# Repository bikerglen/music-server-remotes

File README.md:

Mopidy Music Server and Pianobar Player Remote Track/Artist/Album Display

Mopidy Music Server Remote Control

This repository contains the enclsoure designs, circuit board designs, and software for a Mopidy / Pianobar remote track / artist / album display and a Mopidy remote playback control. Both are based on Particle Photons and connect to the Linux server hosting the applications using Wi-Fi. The display uses scrolling 14-segment LED displays for a retro look. The remote control uses custom-labeled NKK pushbutton switches.

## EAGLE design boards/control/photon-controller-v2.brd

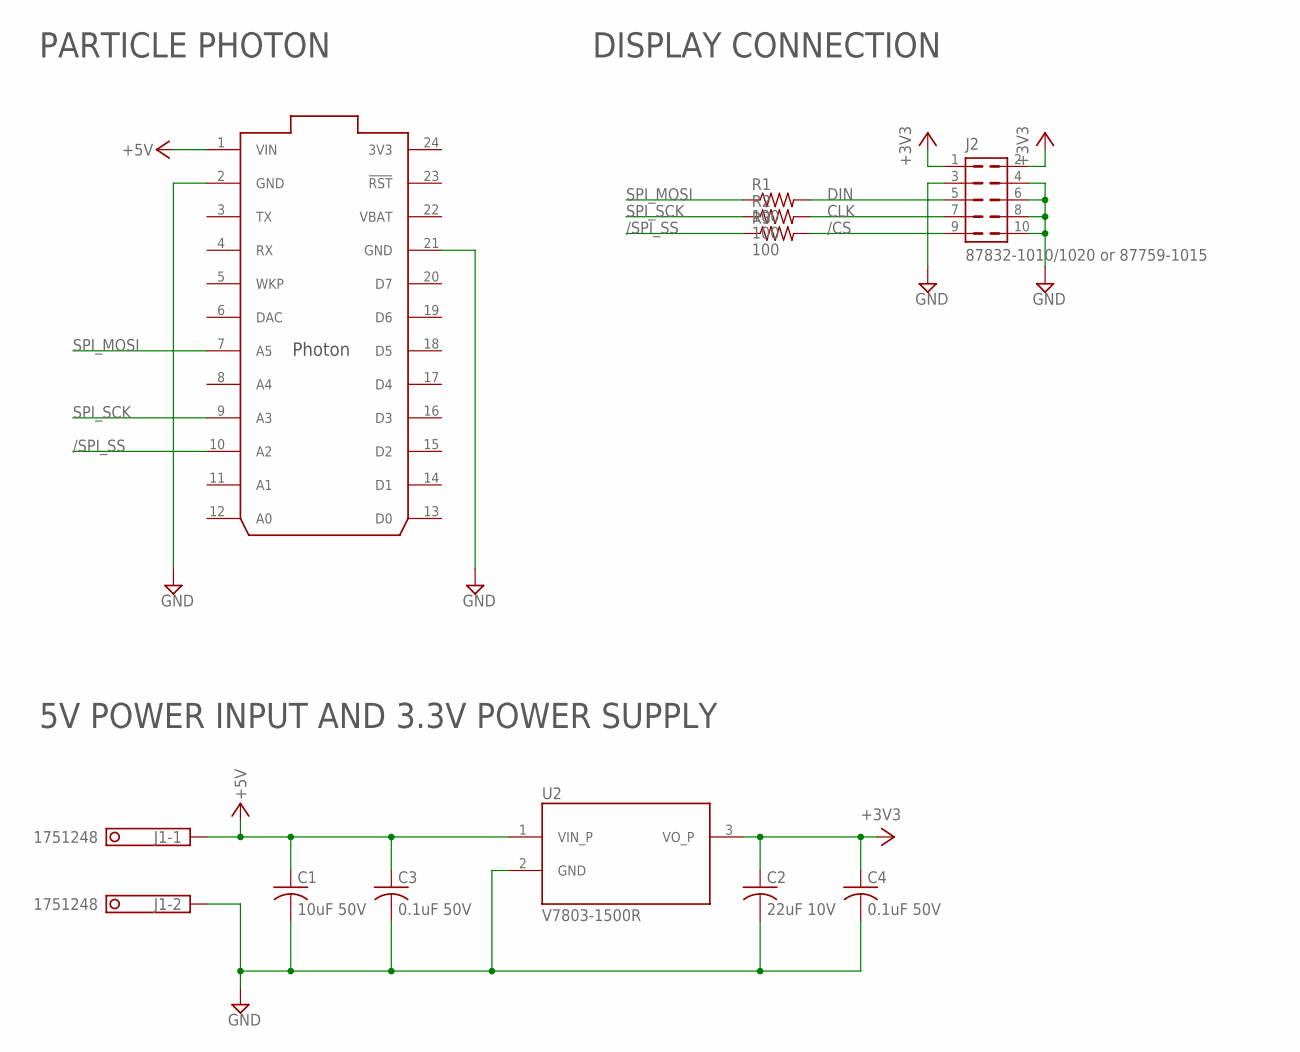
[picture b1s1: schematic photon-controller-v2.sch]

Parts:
C1: 10uF 50V; C1210K; MFR_PART_NO C1210C106K5RACTU
C2: 22uF 10V; C1206K; MFR_PART_NO C1206C226K8RAC7800
C3, C4: 0.1uF 50V; C1206K; MFR_PART_NO C1206S104M5RACTU
J1: 1751248
J2: 87832-1010/1020 or 87759-1015; 87832-10
R1, R2, R3: 100; R1206
U1: PHOTON_WITH_HEADERS; PHOTON
U2: V7803-1500R; CONV_V7803-1500R

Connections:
3V3: U1.24 (3V3)
+3V3: C2.1, C4.1, J2.1, J2.2, U2.3 (VO_P)
+5V: C1.1, C3.1, J1.1, U1.1 (VIN), U2.1 (VIN_P)
/CS: J2.9, R3.2
/SPI_SS: R3.1, U1.10 (A2)
CLK: J2.7, R2.2
DIN: J2.5, R1.2
GND: C1.2, C2.2, C3.2, C4.2, J1.2, J2.3, J2.4, J2.6, J2.8, J2.10, U1.2 (GND), U1.21 (GND), U2.2 (GND)
SPI_MOSI: R1.1, U1.7 (A5)
SPI_SCK: R2.1, U1.9 (A3)
VBAT: U1.22 (VBAT)

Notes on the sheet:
5V POWER INPUT AND 3.3V POWER SUPPLY
PARTICLE PHOTON
DISPLAY CONNECTION

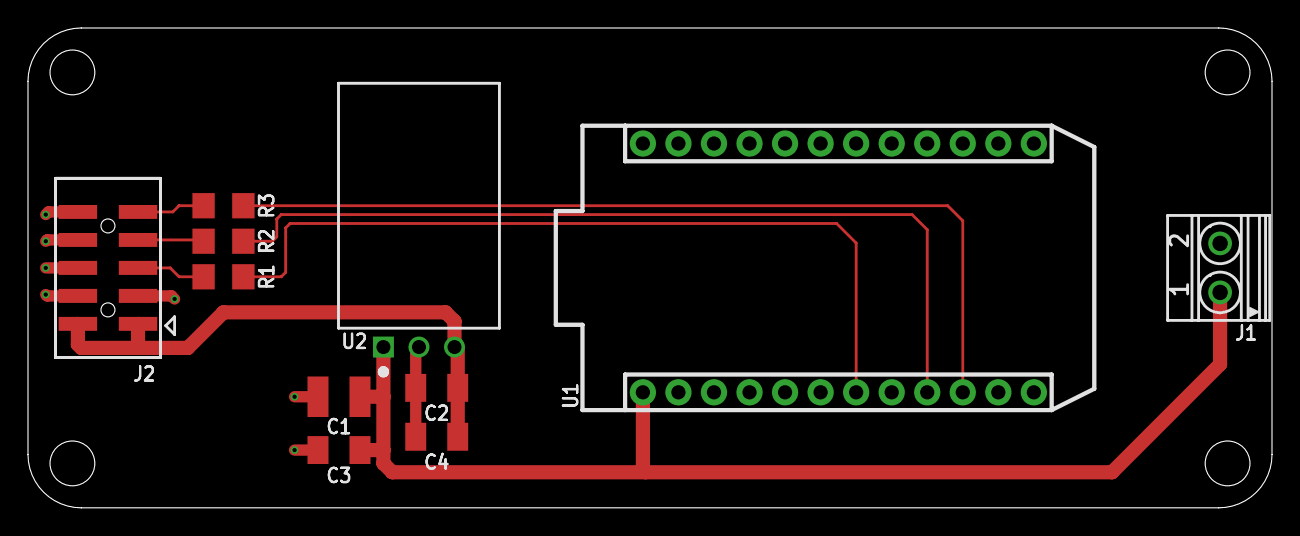
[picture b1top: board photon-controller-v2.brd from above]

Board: 2 copper layers, 88.9 x 34.3 mm, 11 parts (0 on the bottom side), 9 nets.

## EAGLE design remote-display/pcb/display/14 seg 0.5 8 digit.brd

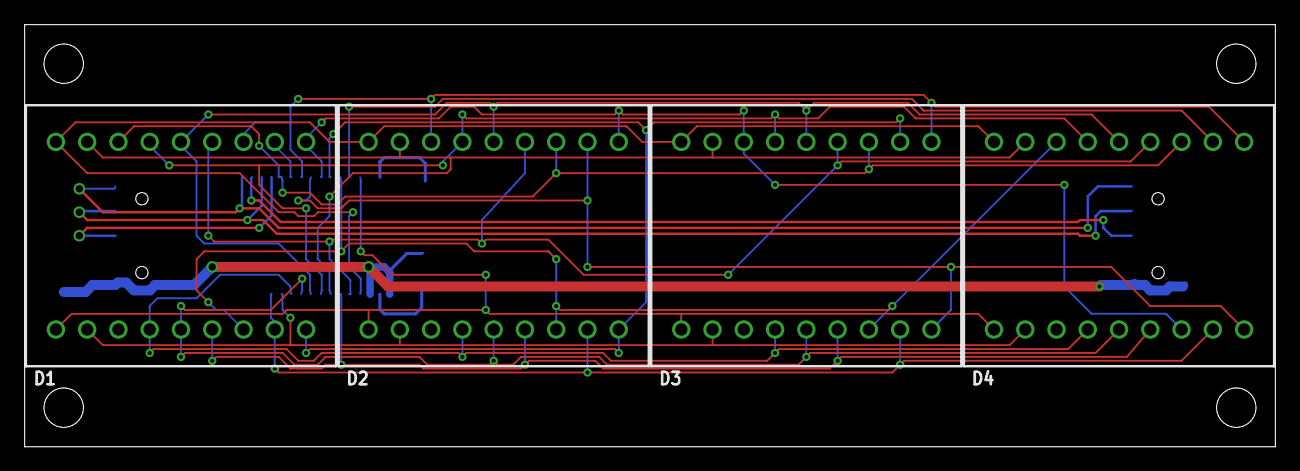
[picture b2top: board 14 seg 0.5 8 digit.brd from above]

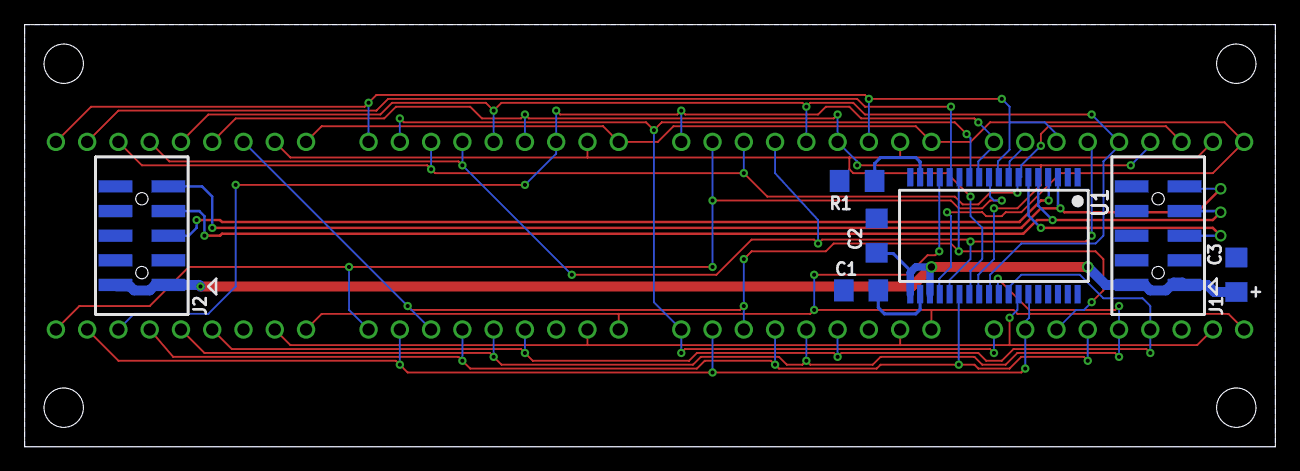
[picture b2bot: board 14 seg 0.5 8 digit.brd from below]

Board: 2 copper layers, 101.6 x 34.3 mm, 11 parts (7 on the bottom side), 27 nets.

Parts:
C1: 22pF; C1206
C2: 0.1uF; C1206
C3: 47uF 10V AVX F931A476MAA; C1206
D1, D2, D3, D4: PCD54-11EWA; PDC54-11
J1, J2: 87832-1010/1020 or 87759-1015; 87832-10
R1: 56k; R1206
U1: MAX6954AAX; MAXIM-0.8-SSOP36

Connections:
+3V3: C2.1, C3.1, J1.1, J1.2, J2.1, J2.2, U1.19, U1.21
/CS: J1.9, J2.9, U1.3
CLK: J1.7, J2.7, U1.5
CSET: C1.1, U1.20
DIN: J1.5, U1.6
DOUT: J2.5, U1.4
GND: C1.2, C2.2, C3.2, J1.3, J1.4, J1.6, J1.8, J1.10, J2.3, J2.4, J2.6, J2.8, J2.10, R1.1, U1.16, U1.18
ISET: R1.2, U1.17
O0: D1.16, D2.12, D3.12, D4.12, U1.7
O1: D1.11, U1.8
O2: D1.12, D2.16, D3.10, D4.10, U1.9
O3: D2.11, D3.9, D4.9, U1.10
O4: D1.10, D2.10, D3.16, D4.7, U1.11
O5: D1.9, D2.9, D3.11, U1.12
O6: D1.7, D2.7, D3.7, D4.16, U1.13
O7: D4.11, U1.14
O8: D1.1, D2.1, D3.1, D4.1, U1.15
O9: D1.18, D2.18, D3.18, D4.18, U1.22
O10: D1.13, D2.13, D3.13, D4.13, U1.23
O11: D1.6, D2.6, D3.6, D4.6, U1.24
O12: D1.17, D2.17, D3.17, D4.17, U1.25
O13: D1.15, D2.15, D3.15, D4.15, U1.26
O14: D1.14, D2.14, D3.14, D4.14, U1.27
O15: D1.5, D2.5, D3.5, D4.5, U1.28
O16: D1.4, D2.4, D3.4, D4.4, U1.29
O17: D1.2, D2.2, D3.2, D4.2, U1.30
O18: D1.8, D2.8, D3.8, D4.8, U1.31

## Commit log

2020-05-26 initial checkin of software source code
2020-06-10 added board and enclosure files
2020-06-10 moved files around
